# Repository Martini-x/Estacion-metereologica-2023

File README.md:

# Anteproyecto: Estacion metereologica   |    Sanchez|Acosta

### Indice 

- [Descripcion del proyecto](#descripcion-del-proyecto)
- [Descripcion de la problematica](#descripcion-de-la-problematica)
- [Caracterisiticas del sistema](#caracterisiticas-del-sistema)
- [Estado del arte / Antecedentes](#estado-del-arte--antecedentes)
- [Estudio de factibilidad](#estudio-de-factibilidad)
- [Diagrama de bloques](#diagrama-de-bloques)
- [Analisis de gastos](#analisis-de-gastos)
- [Planificacion y distribucion de tareas](#planificacion-y-distribucion-de-tareas)

---
## Descripcion del proyecto

### *Descripcion de la problematica:

- Una pequeña estación meteorológica podría solucionar diversas problemáticas relacionadas con la recopilación de datos climáticos y el monitoreo de las condiciones atmosféricas en una ubicación específica. Algunas de las problemáticas que podría abordar son:

  - Predicción del clima local

  - Alertas tempranas de fenómenos meteorológicos extremos

  - Monitoreo de la calidad del aire

  - Investigación científica local

  - Agricultura y gestión del agua

  - Eficiencia energética

  - Seguridad en el transporte

En resumen, una pequeña estación meteorológica puede solucionar problemáticas relacionadas con la falta de datos climáticos precisos y en tiempo real, y puede tener una amplia gama de aplicaciones en diversas áreas, desde la planificación diaria hasta la toma de decisiones críticas en sectores como la agricultura, la investigación científica y la seguridad.

---

### *Caracterisiticas del sistema:
- Una pequeña estación meteorológica generalmente está diseñada para recopilar datos básicos sobre las condiciones climáticas en una ubicación específica. A continuación, se presentan algunas características comunes de una pequeña estación meteorológica:

  - Sensores e instrumentos

  - Transmisión de datos

  - Registro y almacenamiento de datos

  - Alimentación energética
  
  - Durabilidad y protección

  - Interfaz de usuario

  - Conectividad y compatibilidad

- Existen varias mejoras que se podrían implementar en una pequeña estación meteorológica para ampliar su funcionalidad y precisión. Algunas de estas mejoras podrían incluir:

    - Sensores adicionales
    - Comunicación mejorada
    - Integración con sistemas de automatización

    - Interfaz de usuario avanzada

    - Integración con sistemas de alerta temprana

    - Acceso a datos históricos y almacenamiento en la nube

Estas mejoras podrían hacer que la pequeña estación meteorológica sea aún más versátil y valiosa para una variedad de aplicaciones, desde la toma de decisiones en la agricultura y la investigación científica hasta el monitoreo ambiental y la planificación urbana.

---

### *Estado del arte / Antecedentes:

- Durante la busqueda de documentacion para el proyecto, ademas de la busqueda de caracterisiticas, componentes y tecnologias, se buscó estaciones metereologicas ya creadas, se trató de enfocar la busqueda en proyectos a nivel comercial/profesional para informarnos sobre las tecnologias usadas y en proyectos academicos para ver como se aplican dichas tecnologias a un nivel mas amateur.

  - Proyecto comercial: En el mercado existen una infinidad de propuestas de estaciones metereologicas, varian en precios, prestaciones, precision, conectividad, registro, etc. sin embargo existen dos que se asimilan mas a las expectativas sobre el proyecto a realizar.
  
    *[Daza DZWT1081](http://www.sisteco-web.com.ar/products/14-estacion-meteorologica-daza-dzwt1081-wireless.html): Esta estacion permite medir temperatura, humedad, direccion y velocidad del viento, precipitacion, dichas mediciones se muestran mediante un display (Este proyecto abarca los items obligatorios)

    *[Daza DZWH2900](http://www.sisteco-web.com.ar/products/813-estacion-meteorologica-daza-dzwh2900-color-wifi-lux-uv-viento-lluvia-usb.html): Este modelo tiene las mismas prestaciones que el anterior, pero ademas tiene indice UV, alertas para los parametros, previsiones, regsitros, botonera, y conexion wifi para transmision de datos. (Este proyecto abarca los items obligatorios y opcionales)

  - [Proyecto amateur](https://youtu.be/LJszEpV9P0M): Este proyecto tiene algunas de las prestaciones que ofrece una estacion comercial, incluye medicion de temperatura, humedad, direccion y velocidad del viento, precipitacion, indice uv, display y conexion wifi para transmision de datos. Esta seria la expectativa del proyecto a presentar a fin de año.

---

### *Estudio de factibilidad:

  Como ya se vio en la investigacion de los antecedentes de la estacion metereologica existen muchas funciones que se pueden aplicar, pero en el proyecto se van a tomar como esenciales la implementacion de los siguientes items:
  
  -Microcontrolador: Se usara el ESP32 por su buena capacidad de procesamiento, cantidad de perifericos, cantidad de puertos, cantidad de puertos GPIO y mas iportante en este proyecto, comunicacion wifi y bluetooth.
  - Sensores:
    - Temperatura
    - Humedad
    - Precipitacion
    - Direccion del viento
    - Velocidad del viento
    - Presion atmosferica
    - Indice UV
  * Los sensores usados se explican en el diagrama de bloques
  
  - Muestra de Datos mediante display OLED
  - Muestra de datos mediante aplicacipn y pagina web (WIFI)
---

### *Diagrama de bloques:

- Sensores:
  - Temperatura y Humedad: Estas dos variables seran medidas por un mismo sensor en tiempo real. (Htu21d)
  - Precipitacion: Para esta variable se usara un sistema en el cual se ira midiendo la precipitacion de a 2ml, el sistema sera parecido a un "sube y baja", y cada vez que se realice un cambio de movimiento, mediante un iman acoplado a la estructura y a un sensor de efecto hall, se iran contando la cantidad de veces que esto sucede. (A3144)
  - Radiacion solar: Este sensor medira el nivel de radiacion uv en tiempo real, en base a esta medicion se mostrara, ademas del valor, la escala correspondiente de raciacion. (Guva-s12s)
  - Direccion del viento: Esta variable sera sensada con una veleta, para saber la posicion de la veleta se probara con sensores de efecto o con una serie de disco B&W pintados con distintas divisiones indicando distintas posiciones, para saber si el disco en cierta posicion es blanco o negro se usaran sensores infrarrojos. (Efecto hall: A3144) (Infrarrojo: Lm393)
  - Velocidad del viento: Esta variable sera sensada con un anemometro, la velocidad se medira por la cantidad de vueta que se den en un lapso de tiempo, se usara un sensior de efecto hall para saber cuando se dio una vuelta. (A3144)
  - Presion atmosferica: Este sensor medira la presion atmosferica en tiempo real. (BMP280)
 
- Procesamiento y almacenamiento: Todos los datos recibidos por los sensores seran procesados por el microcontrolador ESP32, y opcionalmente guardados en una unidad de almacenamiento. Estos datos seran mostrador por display y una aplicacion y/o pagina web.

- Entrega de datos: La entrega de datos que saldran, una vez procesados por el microcontrolador, seran mostrados por una pequeña pantalla OLED y por una pagina web o aplicacion, en estas dos ultimas se hara uso de la tecnologia WI-FI del micro para que sea posible la transmision de datos de manera inalambrica.

- Interaccion: Este apartado es opcional, pero se tiene pensado que mediante una botonera, el usuario, viendo en la pantalla OLED, pueda navegar entre menues para poder mas y de manera mas comoda la informacion.
---

### *Analisis de gastos:

<div align="center">

 Cant |                       Item                      | Precio
:----:|-------------------------------------------------|---------
 1    |          ESP32 - Wi-Fi & Bluetooth MCU          |  10 U$D*
 2 a 6|      Sensor Efecto Hall A3144                   | 1.5 U$D*
 1    |        Sensor Intensidad Luz Ultravioleta       | 6.5 U$D*
 1    |   Sensor Digital De Humedad Temperatura Htu21d  | 3.5 U$D*
 1    |        Sensor Presion Temperatura Bmp280        |   3 U$D*
 1    |           Conversor De Nivel 5v 3.3v 8ch        | 2.5 U$D*
 3    |         Sensor Optico Velocidad                 | 1.5 U$D*
 1    |       Display OLED                              | 7.5 U$D*
 1    |                  Bateria                        |  10 U$D*
 1    |       Modulo de carga                           | 1.5 U$D*
 1    |   Regulador a 5V                                | 1.8 U$D*
Total |                                                 |  60 U$D*
</div>

---

### *Planificacion y distribucion de tareas:

**Etapas:**
- Prueba de componentes: En esta etapa se van a realizar pruebas de todos los componentes, sensores, alimentacion, comunicacion wifi, etc. En este proceso se va a probar simulando condiciones reales de trabajo, ademas de comenzar a trabar y dominar el nuevo entorno de trabajo con el ESP32.
- Diagramas electronicos: En esta etapa se van a realizar diagramas detallados de todas las conexion del circuito, los cuales seran utiles a la hora de comenzar a trabar con todos los componentes conectados y trabando en conjunto.
- Placas: En este proceso se va a diseñar y crear el shield, en este mismo van a estar las salidas a los sensores, ademas de estar las resistencias para algunos de estos.
- Funcionamiento en conjunto y muestra por display: En esta etapa se van a poner sobre el programa "definitivo" todos los demas programas de prueba previamente creados, se van a adaptar para que puedan trabajar todos de manera uniforme y armoniosa, ademas se mostratan los datos sensados en el display.
- Implementacion de comunicacion: En esta etapa, ya con el programa "definitivo" terminado, se va a implementar la comunicacion mediante wifi para poder visualizar los datos ya sea desde una pagina web o una aplicacion movil.
- Carcasa (Diseño e impresion): En esta estapa se va a diseñar e imprimir en 3D la carcasa de la estacion metereologica, dentro de la misma estara toda la circuiteria y algunos de los sensores utilizados. La carcasa debera cumplir con cierta de resistencia y durabilidad para poder resistir las condiciones adversas de la interperie, ademas debera ser permeable a condiciones desfavorables para el funcionamiento de la estacion, como lo son suciedad, agua, hojas, etc.
- Pruebas: En esta etapa se prevee ya tener todo el proyecto casi terminado para poder realizar todas las pruebas necesarias para garantizar el optimo funcionamiento de la estacion.
- Resolucion de problemas: En esta etapa, en base a la pruebas realizadas en la etapa anterior, se realizaran todas la resoluciones de los problemas que seguramente surjan. En caso de que las problematicas sean pocas o nulas y exista tiempo de sobra, se tratara de trabajar en las implementaciones futuras pensadas.
- Presentacion y documentacion: En esta etapa, mas allá de que a lo largo de todo el proyecto se documenta, se hara enfasis en crear toda la documentacion del proyecto, incluyendo caracteristicas, problematicas, resoluciones, procesos, observacion y todo lo que se crea necesario de documentar. Una vez terminado el informe, se seguira con la presentacion del proyecto, que sera como un pequeño vistazo del informe pero de manera mas amena para garantizar el entendimiento del proyecto de manera considerada.
---

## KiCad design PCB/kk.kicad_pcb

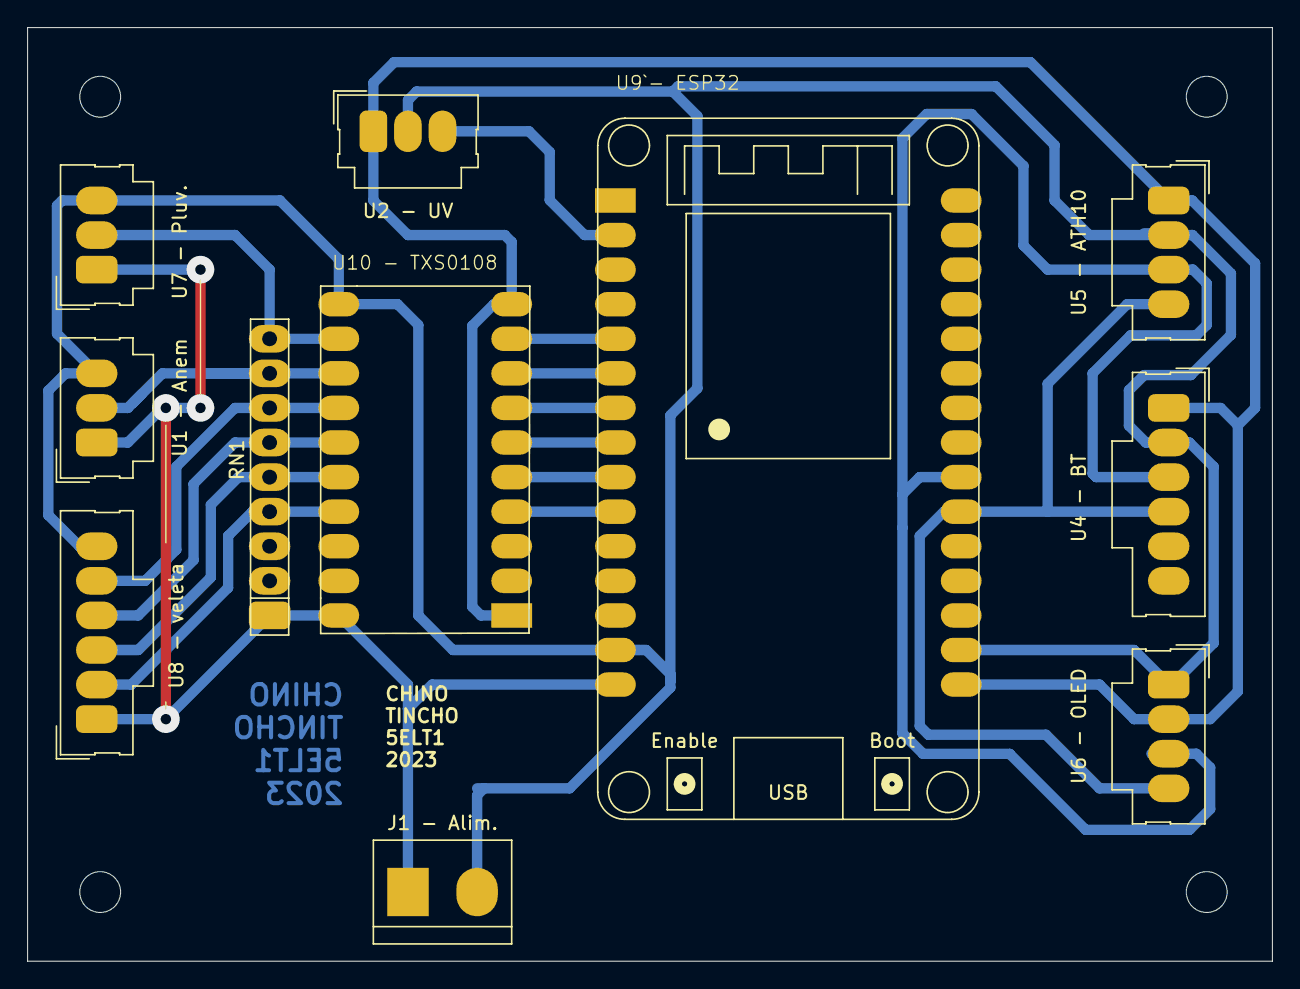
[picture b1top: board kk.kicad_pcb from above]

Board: 2 copper layers, 91.4 x 68.6 mm, 11 parts (0 on the bottom side), 18 nets.

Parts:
J1 - Alim.: Alimentación; Bornera-2_P5.08mm
RN1: R_Network08; R_Array_SIP9
U1 - Anem: ANEMOMETRO; Molex_3_1x03_P2.54mm_Vertical
U2 - UV: GUVA_12S; Molex_3_1x03_P2.54mm_Vertical
U4 - BT: BMP280; Molex_6_1x06_P2.54mm_Vertical
U5 - ATH10: ATH10; Molex_4_1x04_P2.54mm_Vertical
U6 - OLED: Molex_4_1x04_P2.54mm_Vertical
U7 - Pluv.: Pluviómetro; Molex_3_1x03_P2.54mm_Vertical
U8 - veleta: Veleta; Molex_6_1x06_P2.54mm_Vertical
U9`- ESP32: ESP32_DEV1
U10 - TXS0108: TSX0108

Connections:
+3.3V: U2 - UV.1 (VCC), U4 - BT.1 (VCC), U5 - ATH10.1 (VCC), U6 - OLED.2 (VCC), U9`- ESP32.16 (3V3), U10 - TXS0108.1 (VCCA), U10 - TXS0108.10 (OE)
+5V: J1 - Alim..1, RN1.1 (common), U1 - Anem.1 (VCC), U7 - Pluv..1 (VCC), U8 - veleta.1 (VCC), U9`- ESP32.15 (VIN), U10 - TXS0108.20 (VCCB)
/E: RN1.5 (R4), U8 - veleta.3 (H2), U10 - TXS0108.16 (B4)
/N: RN1.4 (R3), U8 - veleta.2 (H1), U10 - TXS0108.17 (B3)
/O: RN1.7 (R6), U8 - veleta.5 (H4), U10 - TXS0108.14 (B6)
/PL: RN1.9 (R8), U7 - Pluv..2 (HALL), U10 - TXS0108.12 (B8)
/S: RN1.6 (R5), U8 - veleta.4 (H3), U10 - TXS0108.15 (B5)
/UV: U2 - UV.3 (OUT), U9`- ESP32.2 (SENSOR_VP)
/VEL: RN1.8 (R7), U1 - Anem.2 (H1), U10 - TXS0108.13 (B7)
Earth: J1 - Alim..2, U1 - Anem.3 (GND), U2 - UV.2 (GND), U4 - BT.2 (GND), U5 - ATH10.2 (GND), U6 - OLED.1 (GND), U7 - Pluv..3 (GND), U8 - veleta.6 (GND), U9`- ESP32.14 (GND), U9`- ESP32.17 (GND), U10 - TXS0108.11 (GND)
unnamed: U4 - BT.3 (SCL), U5 - ATH10.3 (SCL), U6 - OLED.3 (SCL), U9`- ESP32.22 (IO17)
unnamed: U4 - BT.4 (SDA), U5 - ATH10.4 (SDA), U6 - OLED.4 (SDA), U9`- ESP32.21 (IO16)
unnamed: U9`- ESP32.10 (IO27), U10 - TXS0108.4 (A3)
unnamed: U9`- ESP32.9 (IO26), U10 - TXS0108.5 (A4)
unnamed: U9`- ESP32.8 (IO25), U10 - TXS0108.6 (A5)
unnamed: U9`- ESP32.7 (IO33), U10 - TXS0108.7 (A6)
unnamed: U9`- ESP32.6 (IO32), U10 - TXS0108.8 (A7)
unnamed: U9`- ESP32.5 (IO35), U10 - TXS0108.9 (A8)

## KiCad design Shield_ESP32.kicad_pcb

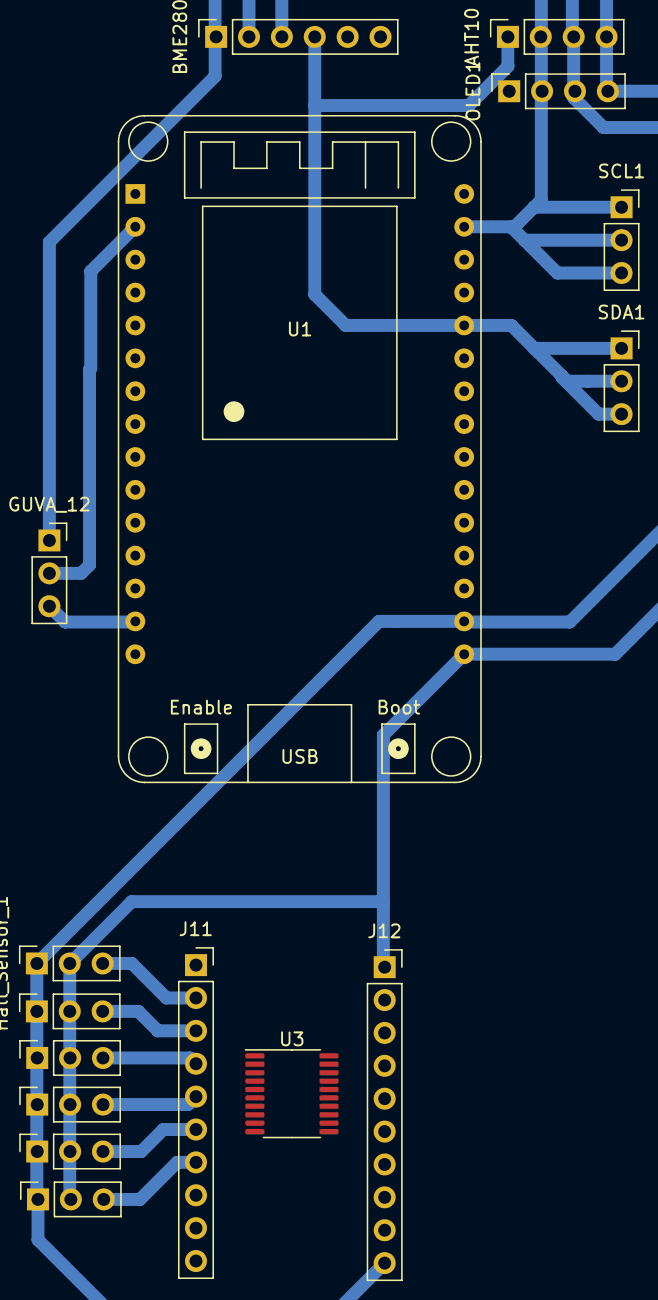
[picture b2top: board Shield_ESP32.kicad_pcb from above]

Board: 2 copper layers, 16 parts (0 on the bottom side), 23 nets.

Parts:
AHT10: Conn_01x04_Pin; PinSocket_1x04_P2.54mm_Vertical
BME280: Conn_01x06_Pin; PinSocket_1x06_P2.54mm_Vertical
GUVA_12: Conn_01x03_Pin; PinSocket_1x03_P2.54mm_Vertical
Hall_Sensor_1, Hall_Sensor_2, Hall_Sensor_3, Hall_Sensor_4, Hall_Sensor_5, Hall_Sensor_6: Conn_01x03_Pin; PinSocket_1x03_P2.54mm_Vertical
J11, J12: Conn_01x10_Pin; PinSocket_1x10_P2.54mm_Vertical
OLED1: Conn_01x04_Pin; PinSocket_1x04_P2.54mm_Vertical
SCL1: Conn_01x03_Pin; PinSocket_1x03_P2.54mm_Vertical
SDA1: Conn_01x03_Pin; PinSocket_1x03_P2.54mm_Vertical
U1: ESP32_DevKit_V1_DOIT; esp32_devkit_v1_doit
U3: TXS0108EPW; TSSOP-20_4.4x6.5mm_P0.65mm

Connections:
+3.3V: AHT10.4, BME280.1, GUVA_12.1, Hall_Sensor_1.2, Hall_Sensor_2.2, Hall_Sensor_3.2, Hall_Sensor_4.2, Hall_Sensor_5.2, Hall_Sensor_6.2, J12.1, OLED1.4, U1.16 (3V3), U3.19 (VCCB)
+5V: J11.1, U1.15 (VIN), U3.2 (VCCA)
GNDREF: AHT10.3, BME280.2, GUVA_12.3, Hall_Sensor_1.1, Hall_Sensor_2.1, Hall_Sensor_3.1, Hall_Sensor_4.1, Hall_Sensor_5.1, Hall_Sensor_6.1, J12.10, OLED1.3, U1.14 (GND), U1.17 (GND), U3.11 (GND)
unnamed: AHT10.1, BME280.4, OLED1.1, SDA1.1, SDA1.2, SDA1.3, U1.26 (IO21)
unnamed: AHT10.2, BME280.3, OLED1.2, SCL1.1, SCL1.2, SCL1.3, U1.29 (IO22)
unnamed: GUVA_12.2, U1.2 (SENSOR_VP)
unnamed: Hall_Sensor_1.3, J11.2, U3.1 (A1)
unnamed: Hall_Sensor_2.3, J11.3, U3.3 (A2)
unnamed: Hall_Sensor_3.3, J11.4, U3.4 (A3)
unnamed: Hall_Sensor_4.3, J11.5, U3.5 (A4)
unnamed: Hall_Sensor_5.3, J11.6, U3.6 (A5)
unnamed: Hall_Sensor_6.3, J11.7, U3.7 (A6)
unnamed: J11.8, U3.8 (A7)
unnamed: J11.9, U3.9 (A8)
unnamed: J11.10, U3.10 (OE)
unnamed: J12.2, U3.20 (B1)
unnamed: J12.3, U3.18 (B2)
unnamed: J12.4, U3.17 (B3)
unnamed: J12.5, U3.16 (B4)
unnamed: J12.6, U3.15 (B5)
unnamed: J12.7, U3.14 (B6)
unnamed: J12.8, U3.13 (B7)
unnamed: J12.9, U3.12 (B8)

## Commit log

2023-08-17 Create Imagenes
2023-08-17 Update Imagenes
2023-08-17 Create a
2023-08-31 Create OLED SCROLL
2023-08-31 Create OLED FONT
2023-08-31 Create OLED
2023-08-31 Create AHT10
2023-08-31 Create Perifericos-Sensores
2023-08-31 Rename PERIFERICOS-SENSORES/OLED to PERIFERICOS-SENSORES/OLED DISPLAY/OLED
2023-08-31 Rename PERIFERICOS-SENSORES/OLED FONT to PERIFERICOS-SENSORES/OLED DISPLAY/OLED FONT
2023-08-31 Rename PERIFERICOS-SENSORES/OLED SCROLL to PERIFERICOS-SENSORES/OLED DISPLAY/OLED SCROLL
2023-08-31 Rename PERIFERICOS-SENSORES/AHT10 to PERIFERICOS-SENSORES/TEMPERATURA-HUMEDAD/AHT10
2023-09-01 Create bmp280
2023-09-01 Create GUVA-S12SD
2023-09-01 Create GUVA-S12SD con Escala UV
2023-09-07 Update OLED SCROLL
2023-09-07 Update AHT10
2023-09-07 Update OLED FONT
2023-09-07 Update OLED
2023-09-07 Update bmp280
2023-09-07 Update GUVA-S12SD con Escala UV
2023-09-08 Create CODIGOD
2023-09-22 Rename ahtx0.py to Librerias/ahtx0.py
2023-10-23 Rename OLED to OLED.py
2023-11-09 Diseño PCB - Esquemático + PCB + Vistas 3d
2024-11-01 Rename kk.kicad_pro to PCB/kk.kicad_pro
